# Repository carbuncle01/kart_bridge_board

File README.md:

# kart_bridge_board Rev.2（低価格版）

`kart_bridge_board`は、RC車両の受信機・サーボ・ESC間に挿入する制御基板です。通常時は受信機のCH1/CH2信号をMANUAL経路で通し、許可条件が成立したときだけSTM32生成PWMへ切り替えます。

| 項目 | Rev.2の定義 |
| --- | --- |
| 正式名称 | `kart_bridge_board` |
| Board ID | `JPBB-01` |
| Revision | `Rev.2` |
| 文書日付 | 2026-07-23 |
| KiCad | 10.0.4以降 |
| 基板外形 | 60 × 30 mm |
| 基板構成 | 4層、1.0 mm |
| 積層 | JLCPCB標準4層（指定なし） |
| 内層 | In1.Cu: 連続GND、In2.Cu: VBEC |
| 表面処理 | Lead-free HASL |
| PCBA実装面 | Top sideのみ |
| 主電源 | J5 pin 2からのTBLE-04SR BEC入力 |
| USB VBUS | D2とU3を介してMCU／3.3 Vロジックを給電。VBEC、MUX、サーボ、ESCからは分離 |
| 既定信号経路 | MANUAL |

旧プロジェクトのRev.1は旧リポジトリのGitタグ`JPBB-01-Rev.1`で管理されていました。この新規リポジトリには旧履歴・タグを含めません。低価格化の差分と注文値は[docs/rev2_cost_optimization.md](docs/rev2_cost_optimization.md)を参照してください。

## ファームウェアをビルドする

このリポジトリはKart用の独立した基板・ファームウェアプロジェクトです。
ROS 2やKart本体のソースはビルドに不要です。

```bash
cd /Users/at/project/tmp/kart_bridge_board
./firmware/scripts/build.sh step8_final
# 全8段階を検証する場合
./firmware/scripts/build.sh all
./firmware/scripts/test.sh
```

依存ソフトの取得と通常のCMakeコマンドは[firmware/README.md](firmware/README.md)を参照してください。
最終版の生成先は `firmware/build/step8_final/step8_final.{elf,hex,bin}` です。
移行範囲・互換性・今回の検証結果は[docs/kart_migration.md](docs/kart_migration.md)に記録します。

## Rev.2の実装方針

- 配線余裕と書き込み操作性を確保するため、外形は60 × 30 mmです。H1/H2は削除し、B面中央の20 × 12 mm領域へ両面テープで固定します。
- 4層・1.0 mmと連続In1 GNDは維持し、JLCPCBの標準積層、標準FR-4 TG135、Lead-free HASLを使用します。製造インピーダンス指定は行いません。
- 全ビアは0.30 mm以上の穴へ統一し、0.20 mm微細ビアによる追加料金を避けます。
- 抵抗とセラミックコンデンサは0402（1005 metric）です。電源バルクのC1だけはPanasonic `EEHZK1E101UP`（100 µF / 25 V、導電性高分子ハイブリッドアルミ電解、LCSC `C454668`）です。
- MCUは同一ピン配置の`STM32G0B1CBT6`（LCSC `C2847904`、128 KiB）です。ファームウェア容量を確認し、旧BOMと混在させないでください。
- C2の追加バルクフットプリントはありません。サーボ突入でVBEC降下が問題になる場合は、外付け対策または次リビジョンで容量・電源構成を見直します。
- USBクロックはSTM32G0B1内蔵HSI48とCRSを使います。外部HSE水晶Y1と負荷コンデンサC12/C13は実装せず、フットプリントもありません。
- 表面テストポイントはTP1〜TP8です。TP9〜TP12はRev.2にありません。
- J1〜J5はPCBA非実装（DNP）で、PCBA後に2.54 mmヘッダーを手はんだします。
- J7はPCBA実装するSamtec `FTSH-105-01-L-DV-007-K`（LCSC `C5296739`）です。Cortex 10-pin SWDの物理position 7を省いたキー付きコネクタで、VTrefは電源入力ではなくターゲット電圧の参照です。
- SW1（RST）とSW2（BOOT）もPCBA実装します。初回だけJ7からオプションバイトを設定すれば、その後はUSB-Cと2個のスイッチでROM USB DFUへ入れます。
- D1/D2でVBECとUSB VBUSを`LOGIC_RAW`へダイオードORし、U3で+3V3を生成します。USBだけでもMCUは動作しますが、VBEC、U2、サーボ、ESCには給電しません。
- U5はVBECを監視し、VBECがTMUX7236の有効範囲へ達するまでMUX出力を無効化します。

## ディレクトリ

```text
hardware/kicad/kart_bridge_board/  KiCadプロジェクトと製造スクリプト
docs/                                  設計・発注・初回通電の注意事項
firmware/                              STM32G0B1用の段階別ファームウェア
tools/                                 補助ツール用の予約領域
```

## 段階別ファームウェア

`firmware/`には、MANUAL固定の起動確認からUSB指令・フェイルセーフを含む
最終版まで、`step1_safe_boot`〜`step8_final`の8段階を収録しています。
初めて接続する場合は、基板上の位置と安全な接続順を含む
[firmware/GETTING_STARTED.md](firmware/GETTING_STARTED.md)から始めてください。
ファームウェアの構成と技術的な確認項目は
[firmware/README.md](firmware/README.md)にまとめています。

## 製造データの生成

macOSのKiCad 10を想定した例です。

```bash
cd hardware/kicad/kart_bridge_board
./scripts/rebuild.sh
```

`rebuild.sh`は回路図、プロジェクト設定、配線済みPCBをソースから再生成して独立監査を行い、続けて`export.sh`を実行します。KiCadファイルを再生成せず製造出力だけを更新する場合は`./scripts/export.sh`を使用します。`fabrication/build/`へ検証レポート、Gerber ZIP、ドリル、JLCPCB用BOM/CPLを生成します。JLCPCBへはGerber ZIP、BOM CSV、CPL CSVをそれぞれ所定欄へアップロードしてください。プロジェクト一式のアーカイブは保管・引き渡し用であり、PCBA注文欄へそのままアップロードするファイルではありません。

2026-07-23のRev.2生成時点では、KiCad 10.0.4でERC Error/Warning 0、DRC Error/Warning 0、未接続0、回路図・PCB差分0、独立基板監査PASSを確認しています。結果は`fabrication/build/reports/build_manifest.txt`へ記録されます。macOS版KiCad 10.0.4で発生するCLIの既知の異常終了には、同版だけで有効になる`run_kicad_drc.sh`の最小互換シムを使用します。このシムはDRC規則や違反を抑制しません。

KiCad CLIのDRCが正常終了したかは、実行時の終了コードと生成された最終レポートで判断してください。レポートがない、CLIが異常終了する、または違反が残る場合は合格扱いにせず、KiCad GUIのDRCを含む再確認が終わるまで発注しません。

## JLCPCBへ発注する前の必須確認

この60 × 30 mm版は、以前の50 × 25 mm版とGerber、BOM、CPLのすべてが異なります。JLCPCBへ以前のデータをアップロード済みの場合は、新規注文または製造開始前の編集で3ファイルを同じビルドのものへ全て差し替えてください。旧Gerberと新BOM/CPLを混在させてはいけません。

1. `export.sh`を発注対象の最終KiCadファイルに対して実行し、ERC、DRC、未接続、回路図・PCB整合性の各チェックが正常終了し、最終レポートに違反が残っていないことを確認する。CLI DRCが異常終了した場合はGUI DRCを実行し、原因と結果を記録する。
2. JLCPCBでは「4層・1.0 mm、標準FR-4 TG135、Lead-free HASL、積層指定なし、インピーダンス指定なし、最小ビア穴0.30 mm」を選ぶ。
3. BOMのLCSC在庫と価格を注文時点で再照合する。U1は`STM32G0B1CBT6` / `C2847904`であることを確認する。特にU2の`TMUX7236PWR` / `C37096021`は在庫が少ない可能性があるため、発注直前の確保または事前購入を検討する。
4. 代替部品を選ぶ場合は、LCSC番号だけでなく、メーカー型番、ピン配置、パッケージ、動作電圧、定格を確認する。自動代替を無条件で承認しない。
5. JLCPCB部品照合画面でUSB-C、MCU、TMUX、USB ESD、LDO、U5、D1/D2、Q1〜Q4、C1、J7、SW1/SW2の実装面、pin 1、回転、極性を確認する。
6. PCBA面をTop sideにし、J1〜J5だけがDNPであること、J7とSW1/SW2は実装対象に含まれることを確認する。
7. 60 × 30 mm外形、USB-Cの張り出し、固定穴が存在しないこと、B面20 × 12 mmテープ領域、工程辺／パネル条件をオンラインGerber Viewerと注文画面で確認する。
8. BEC 1.5 Aは受信機・サーボ・基板を含む系全体の上限です。使用サーボの突入電流とストール電流を実機で確認する。
9. Rev.2にはVBEC入力の逆接保護、ヒューズ／電子過電流保護、車載サージ用TVSがありません。極性と電源条件を治具で確認し、必要な保護は上流側へ設ける。

フェイルセーフの保証範囲と初回通電はRev.1から共通の[docs/design_review.md](docs/design_review.md)、Rev.2の差分は[docs/rev2_cost_optimization.md](docs/rev2_cost_optimization.md)を参照してください。

## 初回書き込みと以後のUSB更新

初回ST-LINK設定からUSB DFU、USB CDC、Step 8の通常運用までの全体像は、
[docs/setup_flow.md](docs/setup_flow.md)を参照してください。

最初の1回はST-LINKとJ7を使います。基板はUSB-CまたはBECから給電し、ST-LINK側からJ7 pin 1へ電源を供給しないでください。STM32CubeProgrammerで接続し、`BOOT_LOCK = 0`、`nBOOT1 = 1`、`nBOOT_SEL = 0`へ設定します。`nBOOT_SEL`が正しい名称であり、`nBOOT0_SEL`ではありません。

以後はMacへUSB-Cで接続し、SW2（BOOT）を押したままSW1（RST）を押して離し、その後SW2を離すとROM USB DFUへ入れます。STM32CubeProgrammerのUSB接続からファームウェアを書き込めます。通常起動時はBOOTを押さず、RSTだけを押します。オプションバイト変更後も復旧用J7は残るため、USB更新に失敗した場合はST-LINKを再接続できます。

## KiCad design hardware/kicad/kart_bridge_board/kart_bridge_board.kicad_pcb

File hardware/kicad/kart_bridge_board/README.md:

# kart_bridge_board Rev.2 — KiCadプロジェクト

| 項目 | 値 |
| --- | --- |
| Board ID | `JPBB-01` |
| Revision | `Rev.2` |
| 外形 | 60 × 30 mm |
| PCB | 4層、1.0 mm |
| 積層 | JLCPCB標準4層（指定なし） |
| 表面処理 | Lead-free HASL |
| PCBA面 | Top side |
| 主電源 | J5 pin 2からのTBLE-04SR BEC |
| USB VBUS | D2/U3経由でMCU／3.3 Vロジックを給電。VBEC、MUX、サーボ、ESCから分離 |
| 既定信号経路 | MANUAL |

Rev.1はGitタグ`JPBB-01-Rev.1`で復元できます。Rev.2の価格差と発注値はリポジトリ直下の`docs/rev2_cost_optimization.md`を参照してください。

## Rev.2固有の注意

- 配線・書き込み操作の余裕を確保するため外形は60 × 30 mm。H1/H2はなく、B面中央の20 × 12 mm平坦領域へ両面テープで固定する。
- 4層・1.0 mmと連続In1 GNDを維持し、JLCPCB標準積層、標準FR-4 TG135、Lead-free HASLを選ぶ。インピーダンス管理は指定しない。
- 全ビア穴径は0.30 mm以上。
- 抵抗とセラミックコンデンサは0402（1005 metric）。C1だけは`EEHZK1E101UP`（100 µF / 25 V、LCSC `C454668`）の導電性高分子ハイブリッドアルミ電解SMD。
- U1は`STM32G0B1CBT6`（LCSC `C2847904`、128 KiB）。ファームウェア容量を確認し、旧BOMと混在させない。
- U2は`TMUX7236PWR`（LCSC `C37096021`）。在庫が少ない可能性があるため、発注直前に在庫を確保する。
- C2、Y1、C12、C13、TP9〜TP12はRev.2に存在しない。
- USBクロックは外部水晶ではなくSTM32G0B1のHSI48/CRSを使う。
- J1〜J5はDNPで、PCBA後に2.54 mmヘッダーを手はんだする。
- J7はSamtec `FTSH-105-01-L-DV-007-K`（LCSC `C5296739`）をPCBA実装する。Cortex SWDの物理position 7を省いたキー付きコネクタで、VTrefは電源入力ではない。
- SW1（RST）とSW2（BOOT）はPCBA実装する。初回だけST-LINKで`BOOT_LOCK=0`、`nBOOT1=1`、`nBOOT_SEL=0`へ設定し、その後はUSB ROM DFUを使用できる。
- D1/D2はVBECとUSB VBUSを`LOGIC_RAW`へダイオードORし、U3が+3V3を生成する。USB単独時はMCUだけを起動し、VBEC系負荷へは給電しない。
- U5はVBECが有効範囲に達するまでTMUX7236の出力を無効化する。
- `USB_DIFF`の線幅0.15 mm / 間隔0.15 mmは短いUSB Full-Speed配線用の名目値で、90 Ω製造保証は付けない。

## 製造出力

```bash
./scripts/rebuild.sh
```

これは回路図、プロジェクト設定、配線済みPCBを再生成し、独立基板監査後に製造出力まで作成します。KiCadファイルを再生成せず製造出力だけを更新する場合は次を使用します。

```bash
./scripts/export.sh
```

`fabrication/build/`の最終レポートを確認してから、Gerber ZIP、BOM CSV、CPL CSVをJLCPCBの各欄へ個別にアップロードします。CLI DRCが異常終了する、レポートが生成されない、または違反が残る場合は合格扱いにせず、KiCad GUIのDRCを含む再確認が終わるまで発注しません。詳細な発注・初回通電条件はリポジトリ直下の`docs/design_review.md`を参照してください。

2026-07-23のRev.2生成時点では、KiCad 10.0.4でERC/DRC、未接続、回路図・PCB差分、独立基板監査、JLCPCB BOM/CPL整合性がすべてPASSしています。`fabrication/build/reports/build_manifest.txt`に集約結果を保存します。macOS版KiCad 10.0.4だけで必要になるCLI互換シムは`run_kicad_drc.sh`が限定適用し、DRC規則や違反は抑制しません。

## 書き込み

J7へST-LINKを接続するときは基板をUSB-CまたはBECで給電し、J7 pin 1（VTref）へST-LINKから電源を供給しません。初回オプション設定後のUSB DFUは、SW2（BOOT）を押したままSW1（RST）を押して離し、続いてSW2を離してからSTM32CubeProgrammerのUSB接続を選びます。詳細はリポジトリ直下の`docs/design_review.md`を参照してください。

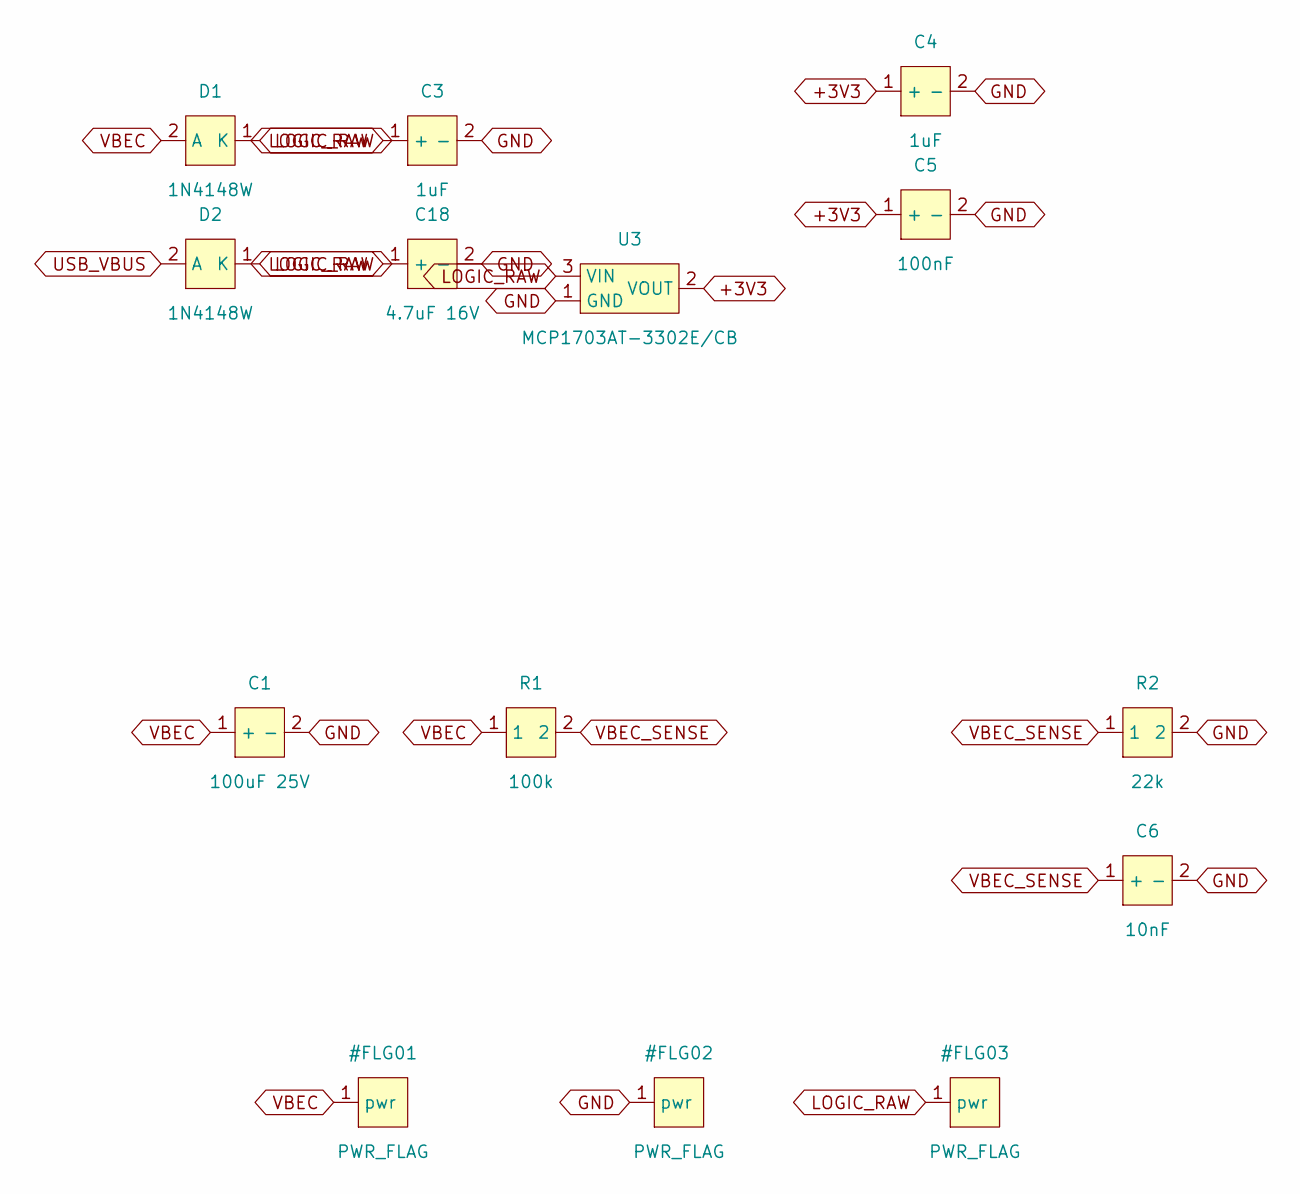
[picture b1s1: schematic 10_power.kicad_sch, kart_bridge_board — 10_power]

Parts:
C1: 100uF 25V; CP_Panasonic_D6.3x5.8; MPN EEHZK1E101UP; LCSC Part # C454668
C3, C4: 1uF; C_0402_1005Metric; MPN CL05A105KA5NQNC; LCSC Part # C52923
C5: 100nF; C_0402_1005Metric; MPN CL05B104KO5NNNC; LCSC Part # C1525
C6: 10nF; C_0402_1005Metric; MPN CL05B103KB5NNNC; LCSC Part # C15195
C18: 4.7uF 16V; C_0603_1608Metric; MPN CL10A475KO8NNNC; LCSC Part # C19666
D1, D2: 1N4148W; D_SOD-123; MPN 1N4148W; LCSC Part # C84367
R1: 100k; R_0402_1005Metric; MPN 0402WGF1003TCE; LCSC Part # C25741
R2: 22k; R_0402_1005Metric; MPN 0402WGF2202TCE; LCSC Part # C25768
U3: MCP1703AT-3302E/CB; SOT-23; MPN MCP1703AT-3302E/CB; LCSC Part # C144183

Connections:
+3V3: C4.1 (+), C5.1 (+), U3.2 (VOUT); also elsewhere on the board
GND: C1.2 (-), C3.2 (-), C4.2 (-), C5.2 (-), C6.2 (-), C18.2 (-), R2.2, U3.1 (GND); also elsewhere on the board
LOGIC_RAW: C3.1 (+), C18.1 (+), D1.1 (K), D2.1 (K), U3.3 (VIN)
USB_VBUS: D2.2 (A); also elsewhere on the board
VBEC: C1.1 (+), D1.2 (A), R1.1; also elsewhere on the board
VBEC_SENSE: C6.1 (+), R1.2, R2.1; also elsewhere on the board

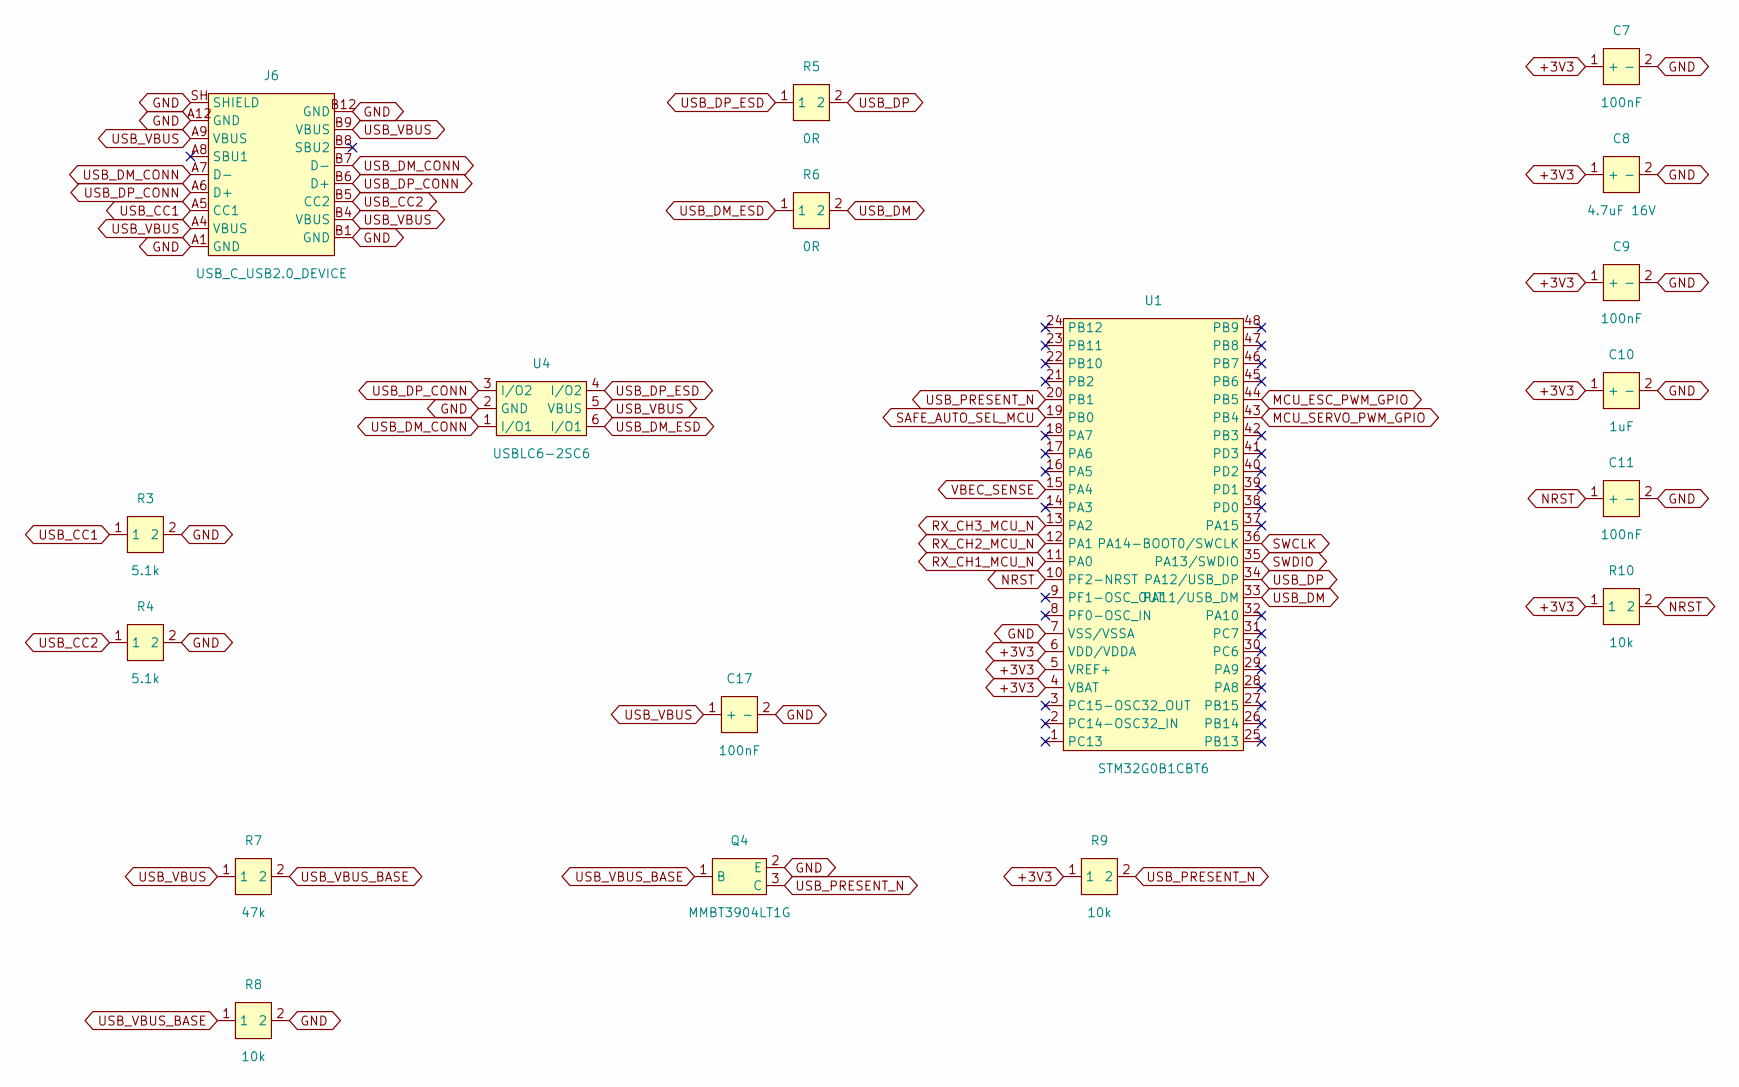
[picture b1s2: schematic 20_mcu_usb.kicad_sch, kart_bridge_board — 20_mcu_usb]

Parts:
C7, C9, C11, C17: 100nF; C_0402_1005Metric; MPN CL05B104KO5NNNC; LCSC Part # C1525
C8: 4.7uF 16V; C_0603_1608Metric; MPN CL10A475KO8NNNC; LCSC Part # C19666
C10: 1uF; C_0402_1005Metric; MPN CL05A105KA5NQNC; LCSC Part # C52923
J6: USB_C_USB2.0_DEVICE; USB_C_Receptacle_HRO_TYPE-C-31-M-12_Edge; MPN TYPE-C-31-M-12; LCSC Part # C165948
Q4: MMBT3904LT1G; SOT-23; MPN MMBT3904LT1G; LCSC Part # C81464
R3, R4: 5.1k; R_0402_1005Metric; MPN 0402WGF5101TCE; LCSC Part # C25905
R5, R6: 0R; R_0402_1005Metric; MPN 0402WGF0000TCE; LCSC Part # C17168
R7: 47k; R_0402_1005Metric; MPN 0402WGF4702TCE; LCSC Part # C25792
R8, R9, R10: 10k; R_0402_1005Metric; MPN 0402WGF1002TCE; LCSC Part # C25744
U1: STM32G0B1CBT6; LQFP-48_7x7mm_P0.5mm; MPN STM32G0B1CBT6; LCSC Part # C2847904
U4: USBLC6-2SC6; SOT-23-6; MPN USBLC6-2SC6; LCSC Part # C7519

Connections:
+3V3: C7.1 (+), C8.1 (+), C9.1 (+), C10.1 (+), R9.1, R10.1, U1.4 (VBAT), U1.5 (VREF+), U1.6 (VDD/VDDA); also elsewhere on the board
GND: C7.2 (-), C8.2 (-), C9.2 (-), C10.2 (-), C11.2 (-), C17.2 (-), J6.A1 (GND), J6.A12 (GND), J6.B1 (GND), J6.B12 (GND), J6.SH (SHIELD), Q4.2 (E), R3.2, R4.2, R8.2, U1.7 (VSS/VSSA), U4.2 (GND); also elsewhere on the board
MCU_ESC_PWM_GPIO: U1.44 (PB5); also elsewhere on the board
MCU_SERVO_PWM_GPIO: U1.43 (PB4); also elsewhere on the board
NRST: C11.1 (+), R10.2, U1.10 (PF2-NRST); also elsewhere on the board
RX_CH1_MCU_N: U1.11 (PA0); also elsewhere on the board
RX_CH2_MCU_N: U1.12 (PA1); also elsewhere on the board
RX_CH3_MCU_N: U1.13 (PA2); also elsewhere on the board
SAFE_AUTO_SEL_MCU: U1.19 (PB0); also elsewhere on the board
SWCLK: U1.36 (PA14-BOOT0/SWCLK); also elsewhere on the board
SWDIO: U1.35 (PA13/SWDIO); also elsewhere on the board
USB_CC1: J6.A5 (CC1), R3.1
USB_CC2: J6.B5 (CC2), R4.1
USB_DM: R6.2, U1.33 (PA11/USB_DM)
USB_DM_CONN: J6.A7 (D-), J6.B7 (D-), U4.1 (I/O1)
USB_DM_ESD: R6.1, U4.6 (I/O1)
USB_DP: R5.2, U1.34 (PA12/USB_DP)
USB_DP_CONN: J6.A6 (D+), J6.B6 (D+), U4.3 (I/O2)
USB_DP_ESD: R5.1, U4.4 (I/O2)
USB_PRESENT_N: Q4.3 (C), R9.2, U1.20 (PB1)
USB_VBUS: C17.1 (+), J6.A4 (VBUS), J6.A9 (VBUS), J6.B4 (VBUS), J6.B9 (VBUS), R7.1, U4.5 (VBUS); also elsewhere on the board
USB_VBUS_BASE: Q4.1 (B), R7.2, R8.1
VBEC_SENSE: U1.15 (PA4); also elsewhere on the board

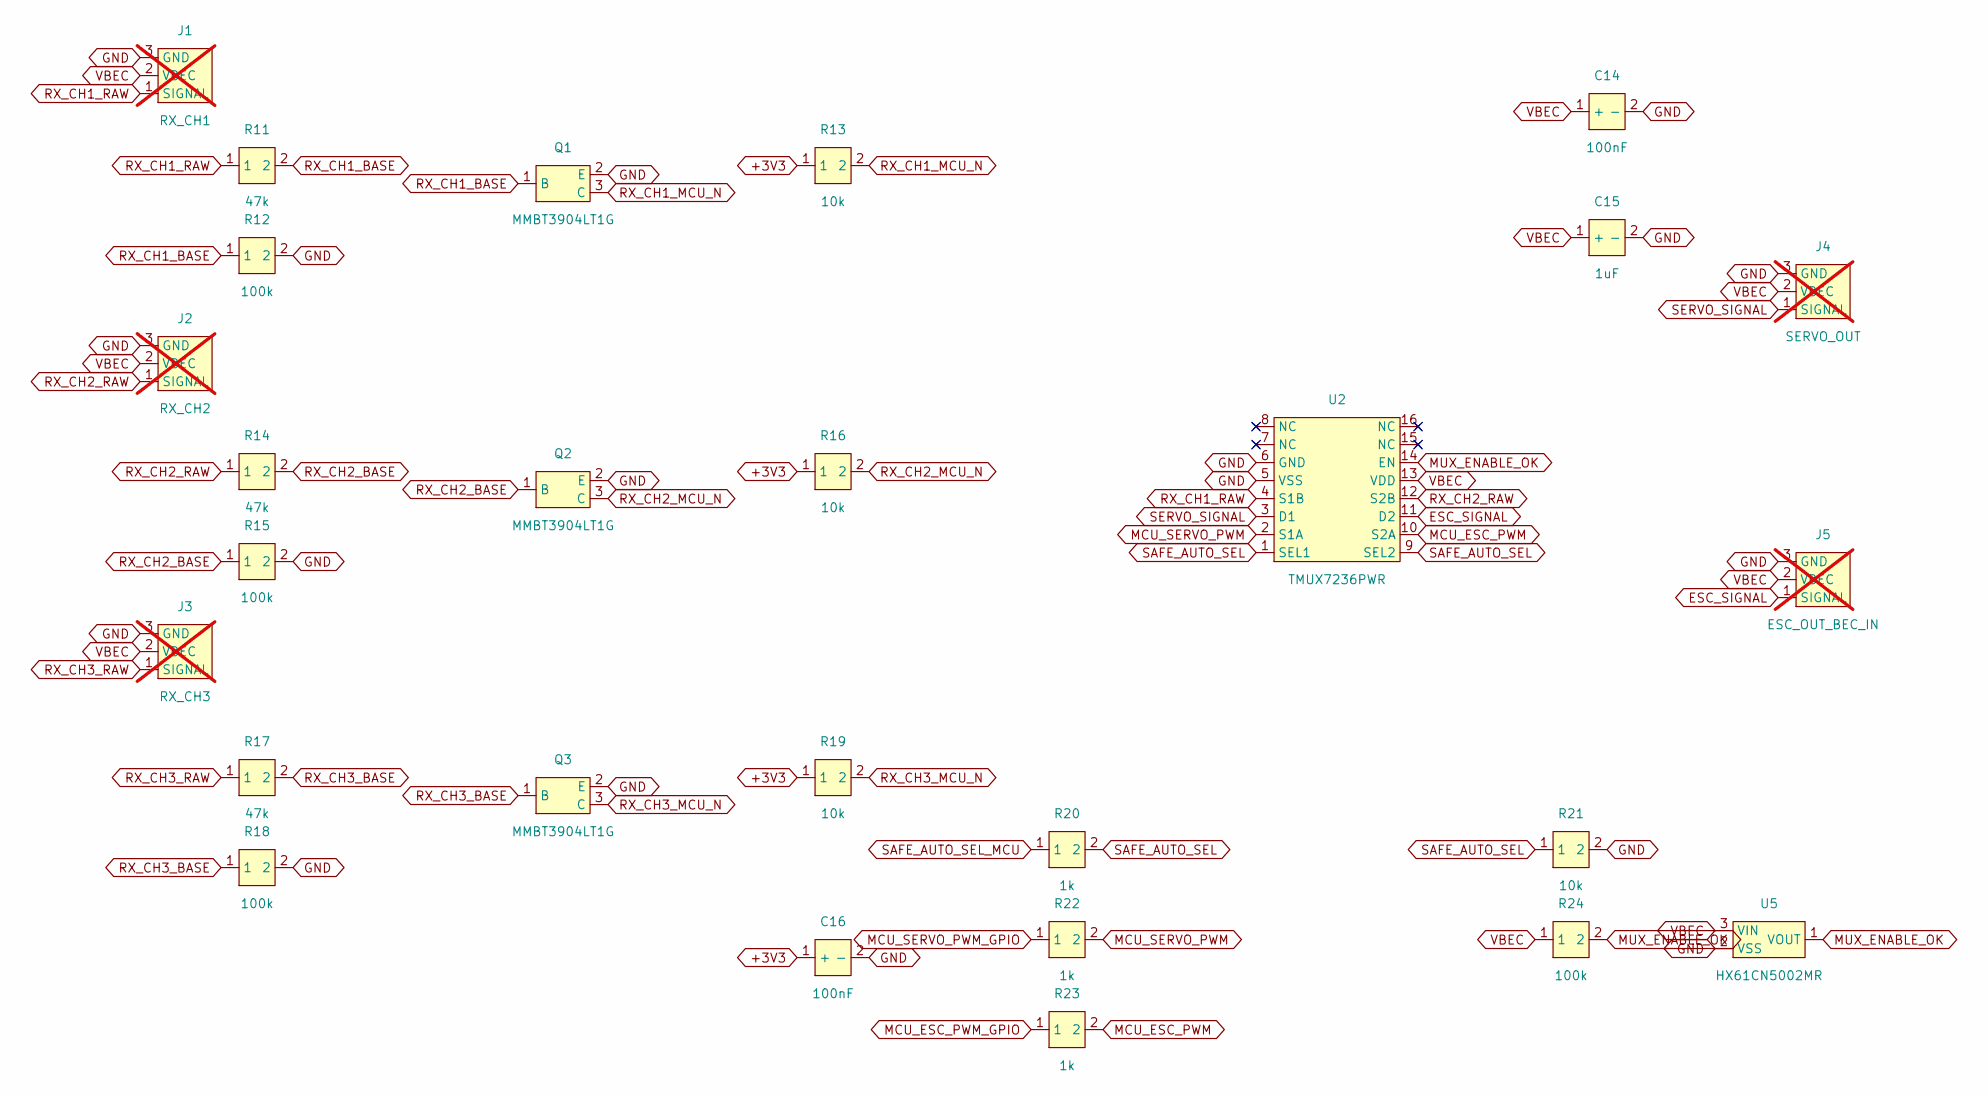
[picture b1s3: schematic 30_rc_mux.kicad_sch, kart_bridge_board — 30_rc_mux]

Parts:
C14, C16: 100nF; C_0402_1005Metric; MPN CL05B104KO5NNNC; LCSC Part # C1525
C15: 1uF; C_0402_1005Metric; MPN CL05A105KA5NQNC; LCSC Part # C52923
J1: RX_CH1; RC_Header_1x03_P2.54mm; MPN 2.54-1*3P Pin; not fitted
J2: RX_CH2; RC_Header_1x03_P2.54mm; MPN 2.54-1*3P Pin; not fitted
J3: RX_CH3; RC_Header_1x03_P2.54mm; MPN 2.54-1*3P Pin; not fitted
J4: SERVO_OUT; RC_Header_1x03_P2.54mm; MPN 2.54-1*3P Pin; not fitted
J5: ESC_OUT_BEC_IN; RC_Header_1x03_P2.54mm; MPN 2.54-1*3P Pin; not fitted
Q1, Q2, Q3: MMBT3904LT1G; SOT-23; MPN MMBT3904LT1G; LCSC Part # C81464
R11, R14, R17: 47k; R_0402_1005Metric; MPN 0402WGF4702TCE; LCSC Part # C25792
R12, R15, R18, R24: 100k; R_0402_1005Metric; MPN 0402WGF1003TCE; LCSC Part # C25741
R13, R16, R19, R21: 10k; R_0402_1005Metric; MPN 0402WGF1002TCE; LCSC Part # C25744
R20, R22, R23: 1k; R_0402_1005Metric; MPN 0402WGF1001TCE; LCSC Part # C11702
U2: TMUX7236PWR; TSSOP-16_4.4x5mm_P0.65mm; MPN TMUX7236PWR; LCSC Part # C37096021
U5: HX61CN5002MR; SOT-23; MPN HX61CN5002MR; LCSC Part # C47344213

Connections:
+3V3: C16.1 (+), R13.1, R16.1, R19.1; also elsewhere on the board
ESC_SIGNAL: J5.1 (SIGNAL), U2.11 (D2); also elsewhere on the board
GND: C14.2 (-), C15.2 (-), C16.2 (-), J1.3 (GND), J2.3 (GND), J3.3 (GND), J4.3 (GND), J5.3 (GND), Q1.2 (E), Q2.2 (E), Q3.2 (E), R12.2, R15.2, R18.2, R21.2, U2.5 (VSS), U2.6 (GND), U5.2 (VSS); also elsewhere on the board
MCU_ESC_PWM: R23.2, U2.10 (S2A)
MCU_ESC_PWM_GPIO: R23.1; also elsewhere on the board
MCU_SERVO_PWM: R22.2, U2.2 (S1A)
MCU_SERVO_PWM_GPIO: R22.1; also elsewhere on the board
MUX_ENABLE_OK: R24.2, U2.14 (EN), U5.1 (VOUT)
RX_CH1_BASE: Q1.1 (B), R11.2, R12.1
RX_CH1_MCU_N: Q1.3 (C), R13.2; also elsewhere on the board
RX_CH1_RAW: J1.1 (SIGNAL), R11.1, U2.4 (S1B); also elsewhere on the board
RX_CH2_BASE: Q2.1 (B), R14.2, R15.1
RX_CH2_MCU_N: Q2.3 (C), R16.2; also elsewhere on the board
RX_CH2_RAW: J2.1 (SIGNAL), R14.1, U2.12 (S2B); also elsewhere on the board
RX_CH3_BASE: Q3.1 (B), R17.2, R18.1
RX_CH3_MCU_N: Q3.3 (C), R19.2; also elsewhere on the board
RX_CH3_RAW: J3.1 (SIGNAL), R17.1; also elsewhere on the board
SAFE_AUTO_SEL: R20.2, R21.1, U2.1 (SEL1), U2.9 (SEL2)
SAFE_AUTO_SEL_MCU: R20.1; also elsewhere on the board
SERVO_SIGNAL: J4.1 (SIGNAL), U2.3 (D1); also elsewhere on the board
VBEC: C14.1 (+), C15.1 (+), J1.2 (VBEC), J2.2 (VBEC), J3.2 (VBEC), J4.2 (VBEC), J5.2 (VBEC), R24.1, U2.13 (VDD), U5.3 (VIN); also elsewhere on the board

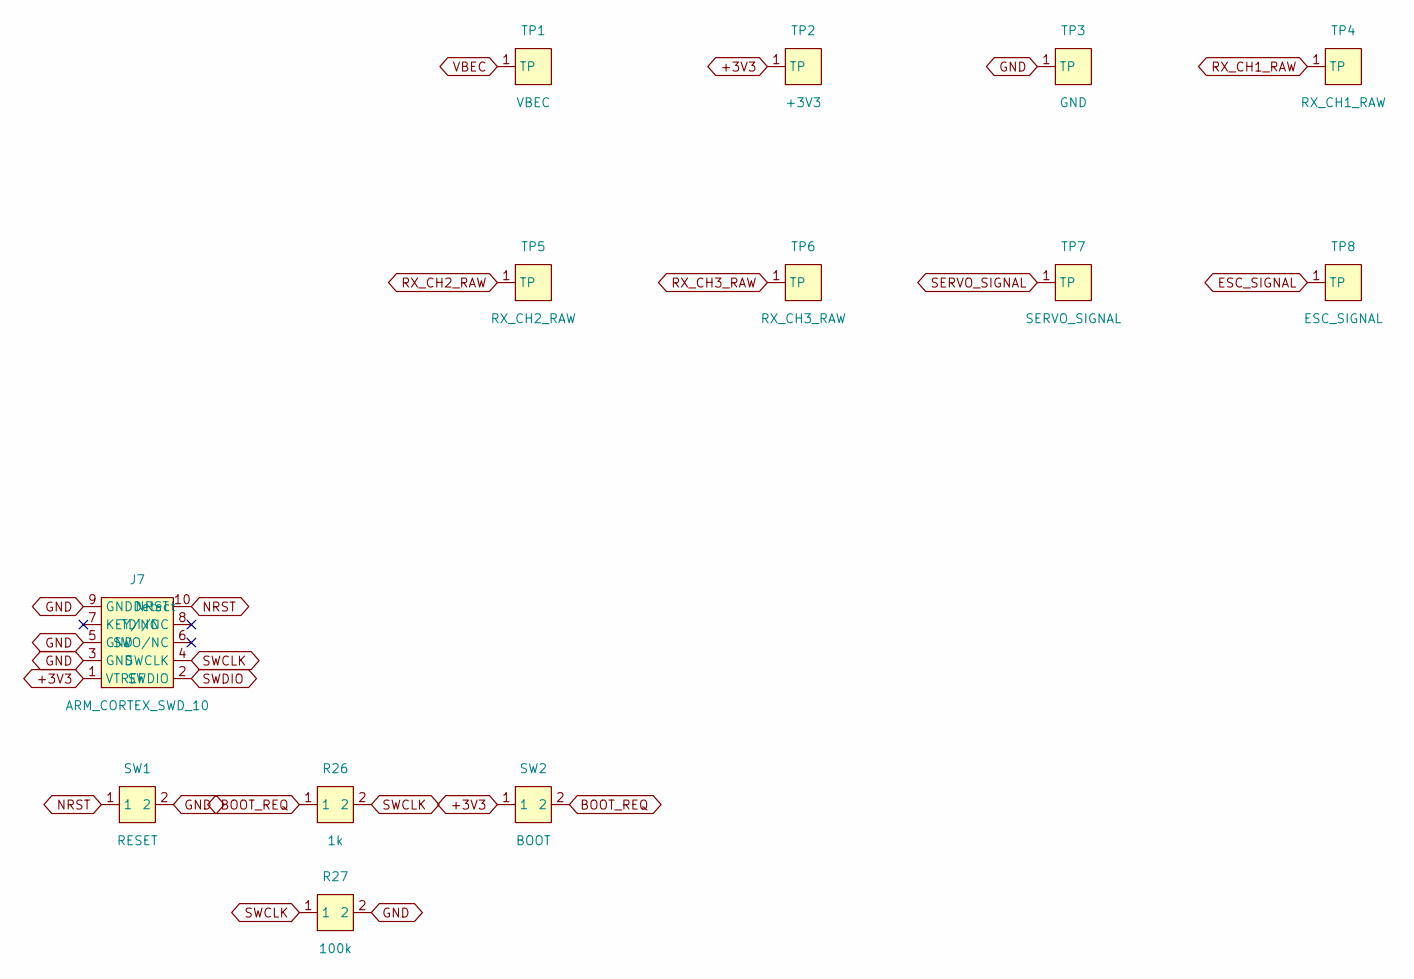
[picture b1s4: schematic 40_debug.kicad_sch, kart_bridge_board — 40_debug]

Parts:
J7: ARM_CORTEX_SWD_10; Samtec_FTSH-105-01-L-DV-007-K; MPN FTSH-105-01-L-DV-007-K; LCSC Part # C5296739
R26: 1k; R_0402_1005Metric; MPN 0402WGF1001TCE; LCSC Part # C11702
R27: 100k; R_0402_1005Metric; MPN 0402WGF1003TCE; LCSC Part # C25741
SW1: RESET; SW_SPST_TS-1088-xR020; MPN TS-1088-AR02016; LCSC Part # C720477
SW2: BOOT; SW_SPST_TS-1088-xR020; MPN TS-1088-AR02016; LCSC Part # C720477
TP1: VBEC; TP_SMD_D1.0mm
TP2: +3V3; TP_SMD_D1.0mm
TP3: GND; TP_SMD_D1.0mm
TP4: RX_CH1_RAW; TP_SMD_D1.0mm
TP5: RX_CH2_RAW; TP_SMD_D1.0mm
TP6: RX_CH3_RAW; TP_SMD_D1.0mm
TP7: SERVO_SIGNAL; TP_SMD_D1.0mm
TP8: ESC_SIGNAL; TP_SMD_D1.0mm

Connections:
+3V3: J7.1 (VTREF), SW2.1, TP2.1; also elsewhere on the board
BOOT_REQ: R26.1, SW2.2
ESC_SIGNAL: TP8.1; also elsewhere on the board
GND: J7.3 (GND), J7.5 (GND), J7.9 (GNDDetect), R27.2, SW1.2, TP3.1; also elsewhere on the board
NRST: J7.10 (NRST), SW1.1; also elsewhere on the board
RX_CH1_RAW: TP4.1; also elsewhere on the board
RX_CH2_RAW: TP5.1; also elsewhere on the board
RX_CH3_RAW: TP6.1; also elsewhere on the board
SERVO_SIGNAL: TP7.1; also elsewhere on the board
SWCLK: J7.4 (SWCLK), R26.2, R27.1; also elsewhere on the board
SWDIO: J7.2 (SWDIO); also elsewhere on the board
VBEC: TP1.1; also elsewhere on the board

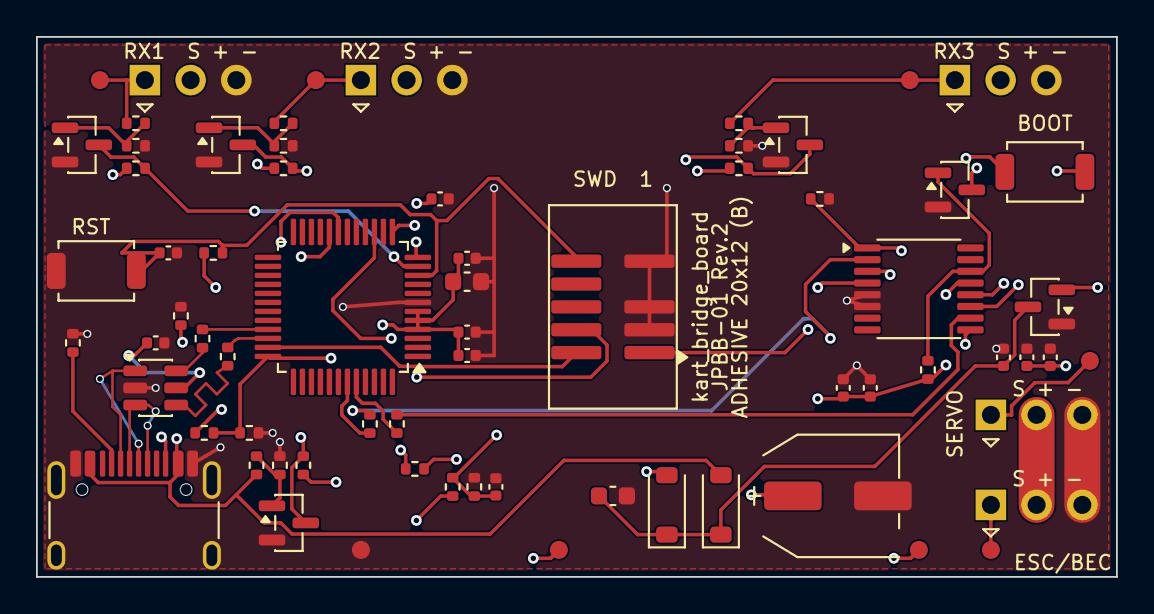
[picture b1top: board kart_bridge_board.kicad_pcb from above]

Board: 4 copper layers, 60.0 x 30.0 mm, 69 parts (0 on the bottom side), 38 nets.

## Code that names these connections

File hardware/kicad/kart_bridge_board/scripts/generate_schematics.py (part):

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
MCU_PIN_NAMES = [
    "PC13", "PC14-OSC32_IN", "PC15-OSC32_OUT", "VBAT", "VREF+", "VDD/VDDA",
    "VSS/VSSA", "PF0-OSC_IN", "PF1-OSC_OUT", "PF2-NRST", "PA0", "PA1",
    "PA2", "PA3", "PA4", "PA5", "PA6", "PA7", "PB0", "PB1", "PB2",
    "PB10", "PB11", "PB12", "PB13", "PB14", "PB15", "PA8", "PA9",
    "PC6", "PC7", "PA10", "PA11/USB_DM", "PA12/USB_DP", "PA13/SWDIO",
    "PA14-BOOT0/SWCLK", "PA15", "PD0", "PD1", "PD2", "PD3", "PB3",
    "PB4", "PB5", "PB6", "PB7", "PB8", "PB9",
]


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    ),
    "Conn_01x03": SymbolDef(
        "Conn_01x03", "J",
        [Pin("1", "SIGNAL"), Pin("2", "VBEC"), Pin("3", "GND")],
        body_width=7.62,
    ),
    "Conn_01x05": SymbolDef(
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                  "Package_TO_SOT_SMD:SOT-23", manufacturer="Microchip Technology",
                  mpn="MCP1703AT-3302E/CB", lcsc="C144183",
                  datasheet="https://ww1.microchip.com/downloads/aemDocuments/documents/APID/ProductDocuments/DataSheets/MCP1703-Data-Sheet-DS20005122.pdf",
                  notes="SOT-23A: Pin 1 GND, Pin 2 VOUT, Pin 3 VIN; LOGIC_RAW is diode-OR powered"),
        Component("D_Schottky", "D1", "1N4148W", (68.58, 40.64),
                  {"1": "LOGIC_RAW", "2": "VBEC"}, "Diode_SMD:D_SOD-123",
                  manufacturer="MDD(Microdiode Semiconductor)", mpn="1N4148W", lcsc="C84367",
                  datasheet="https://jlcpcb.com/partdetail/MDD_Microdiode_Semiconductor-1N4148W/C84367",
                  notes="Low-leakage VBEC-to-logic OR diode; Pin 1 cathode at LOGIC_RAW"),
        Component("D_Schottky", "D2", "1N4148W", (68.58, 53.34),
                  {"1": "LOGIC_RAW", "2": "USB_VBUS"}, "Diode_SMD:D_SOD-123",
                  manufacturer="MDD(Microdiode Semiconductor)", mpn="1N4148W", lcsc="C84367",
                  datasheet="https://jlcpcb.com/partdetail/MDD_Microdiode_Semiconductor-1N4148W/C84367",
                  notes="Low-leakage USB-to-logic OR diode; Pin 1 cathode at LOGIC_RAW"),
        c("C1", "100uF 25V", (73.66, 101.6), "VBEC", "GND", lcsc="C454668",
          footprint="JPBB:CP_Panasonic_D6.3x5.8", manufacturer="Panasonic",
          mpn="EEHZK1E101UP",
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        c("C6", "10nF", (165.1, 116.84), "VBEC_SENSE", "GND",
          notes="ADC anti-noise filter"),
        Component("PWR_FLAG", "#FLG01", "PWR_FLAG", (86.36, 139.7), {"1": "VBEC"},
                  in_bom=False, on_board=False, notes="J5 Pin 2 is the VBEC source"),
        Component("PWR_FLAG", "#FLG02", "PWR_FLAG", (116.84, 139.7), {"1": "GND"},
                  in_bom=False, on_board=False, notes="Ground reference source for ERC"),
        Component("PWR_FLAG", "#FLG03", "PWR_FLAG", (147.32, 139.7), {"1": "LOGIC_RAW"},
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        "15": "VBEC_SENSE",
        "19": "SAFE_AUTO_SEL_MCU", "20": "USB_PRESENT_N", "33": "USB_DM",
        "34": "USB_DP", "35": "SWDIO", "36": "SWCLK",
        "43": "MCU_SERVO_PWM_GPIO", "44": "MCU_ESC_PWM_GPIO",
    })
    usb_nets = {
        "A1": "GND", "A4": "USB_VBUS", "A5": "USB_CC1",
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                  "Package_QFP:LQFP-48_7x7mm_P0.5mm", manufacturer="STMicroelectronics",
                  mpn="STM32G0B1CBT6", lcsc="C2847904",
                  datasheet="https://www.st.com/resource/en/datasheet/stm32g0b1cb.pdf",
                  notes="USB FS MCU; 128 KiB cost-optimized variant; TIM2 CH1/2/3 inputs; PB4/PB5 TIM3 CH1/2 PWM outputs; firmware must fit 128 KiB"),
        Component("USB_C", "J6", "USB_C_USB2.0_DEVICE", (53.34, 50.8), usb_nets,
                  "JPBB:USB_C_Receptacle_HRO_TYPE-C-31-M-12_Edge",
                  manufacturer="Korean Hroparts Elec", mpn="TYPE-C-31-M-12", lcsc="C165948",
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
def rc_mux_components() -> list[Component]:
    connector_fp = "JPBB:RC_Header_1x03_P2.54mm"
    connector_notes = "Hand solder after PCBA; Pin 1 SIG, Pin 2 VBEC, Pin 3 GND"
    components: list[Component] = [
        Component("Conn_01x03", "J1", "RX_CH1", (25.4, 30.48),
                  {"1": "RX_CH1_RAW", "2": "VBEC", "3": "GND"}, connector_fp,
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          notes="Series isolation from MCU GPIO to tied TMUX SEL1/SEL2"),
        r("R21", "10k", (220.98, 139.7), "SAFE_AUTO_SEL", "GND",
          notes="Hardware default to MANUAL during reset/unpowered MCU"),
        r("R22", "1k", (149.86, 152.4), "MCU_SERVO_PWM_GPIO", "MCU_SERVO_PWM",
          notes="Limits fault current between MCU and powered signal mux"),
        r("R23", "1k", (149.86, 165.1), "MCU_ESC_PWM_GPIO", "MCU_ESC_PWM",
          notes="Limits fault current between MCU and powered signal mux"),
        r("R24", "100k", (220.98, 152.4), "VBEC", "MUX_ENABLE_OK",
          notes="Pull-up for U5 open-drain power-good output and TMUX EN"),
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        r("R26", "1k", (83.82, 149.86), "BOOT_REQ", "SWCLK",
          notes="Isolates the BOOT pushbutton branch from the SWD clock line"),
        r("R27", "100k", (83.82, 165.1), "SWCLK", "GND",
          notes="Hardware BOOT0 default low; PA14 is shared with SWCLK"),
    ]
    tp_nets = [
        "VBEC", "+3V3", "GND", "RX_CH1_RAW", "RX_CH2_RAW", "RX_CH3_RAW",
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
